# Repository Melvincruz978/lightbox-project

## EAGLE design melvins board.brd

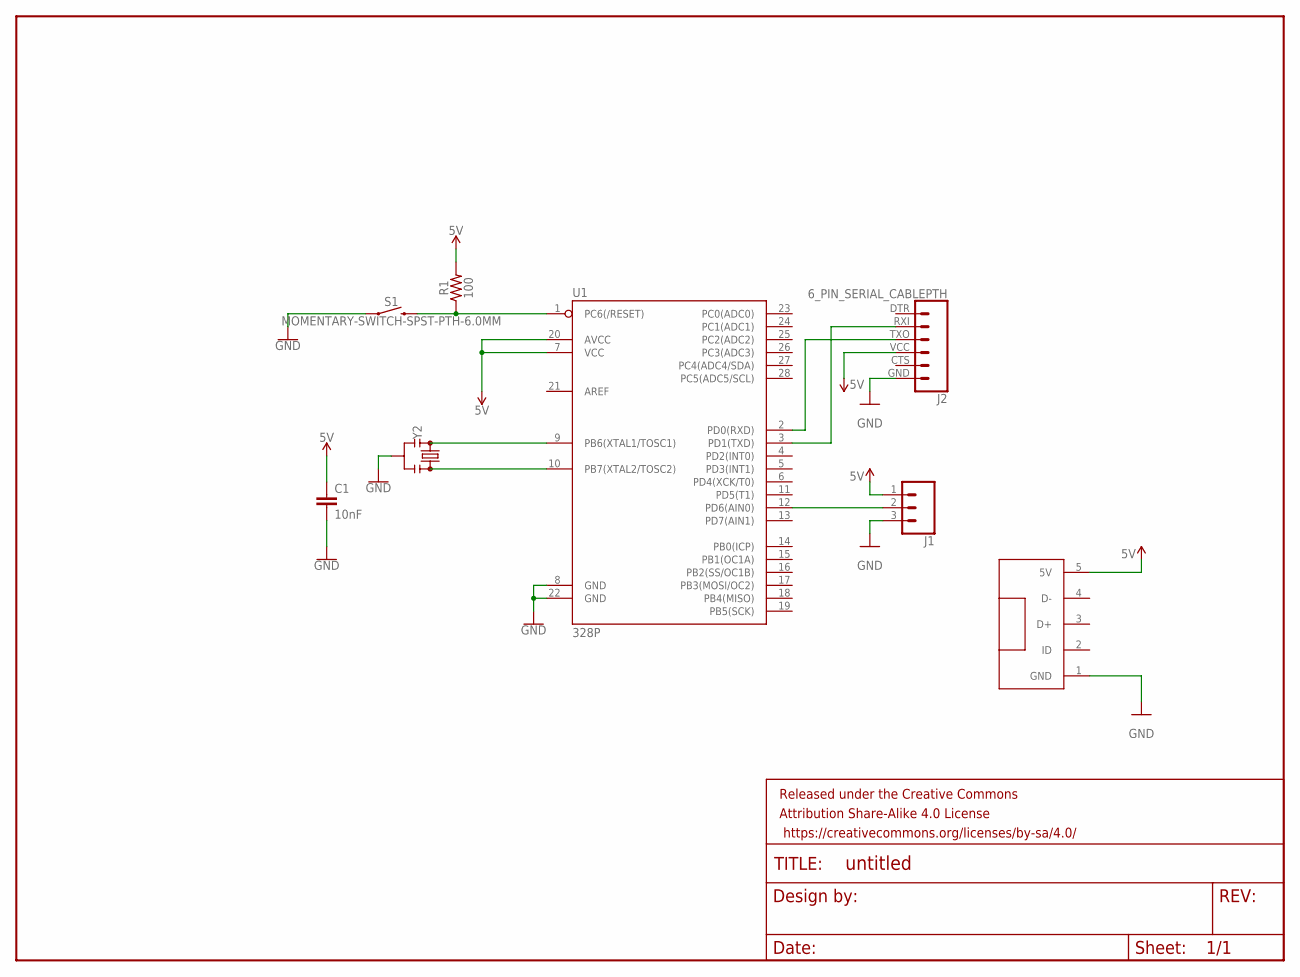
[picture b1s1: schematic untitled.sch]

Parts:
C1: 10nF; CAP-PTH-10MM
FRAME1: FRAME-LETTER; CREATIVE_COMMONS
J1: CONN_03; 1X03
J2: 6_PIN_SERIAL_CABLEPTH; FTDI_BASIC
R1: 100; AXIAL-0.3
S1: MOMENTARY-SWITCH-SPST-PTH-6.0MM; TACTILE_SWITCH_PTH_6.0MM
U1: 328P; DIP28
U$1: USBPORT; USB
Y2: RESONATORPTH-7.6X3.8; RESONATOR-PTH-7.6X3.8

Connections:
5V: C1.1, J1.1, J2.VCC (4), R1.P$2 (2), U1.7 (VCC), U1.20 (AVCC), U$1.5 (5V)
GND: C1.2, J1.3, J2.GND (6), S1.1, U1.8 (GND), U1.22 (GND), U$1.1 (GND), Y2.2
unnamed: R1.P$1 (1), S1.3 (2), U1.1 (PC6(/RESET))
unnamed: J1.2, U1.12 (PD6(AIN0))
unnamed: U1.9 (PB6(XTAL1/TOSC1)), Y2.1
unnamed: U1.10 (PB7(XTAL2/TOSC2)), Y2.3
unnamed: J2.RXI (2), U1.3 (PD1(TXD))
unnamed: J2.TXO (3), U1.2 (PD0(RXD))

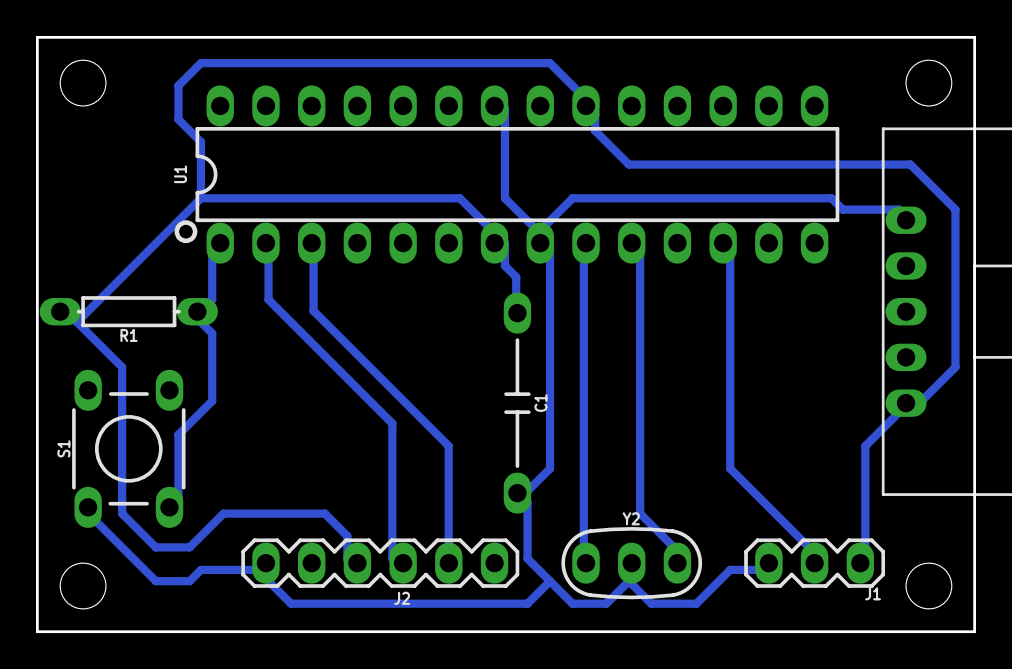
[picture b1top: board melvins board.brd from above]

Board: 2 copper layers, 52.1 x 33.0 mm, 9 parts (0 on the bottom side), 8 nets.

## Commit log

2019-02-13 Added the right ones

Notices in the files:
parts and their libraries:
SparkFun-Aesthetics: Licensing: Creative Commons ShareAlike 4.0 International - https://creativecommons.org/licenses/by-sa/4.0
SparkFun-Aesthetics: Released under the Creative Commons Attribution Share-Alike 4.0 License
SparkFun-Aesthetics: https://creativecommons.org/licenses/by-sa/4.0
